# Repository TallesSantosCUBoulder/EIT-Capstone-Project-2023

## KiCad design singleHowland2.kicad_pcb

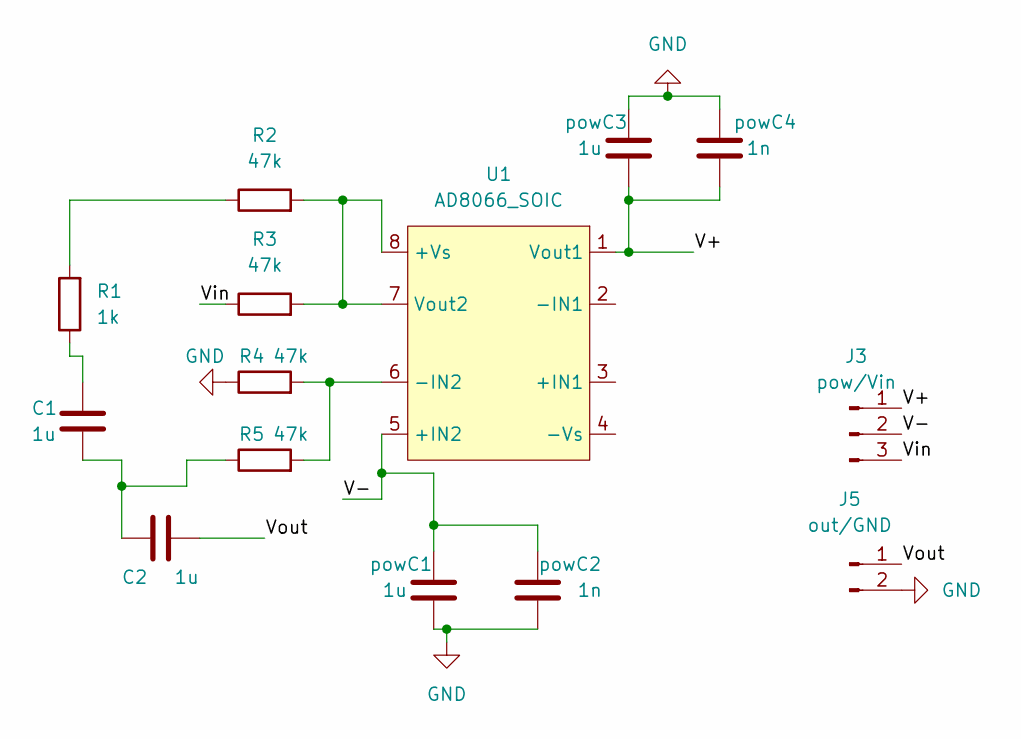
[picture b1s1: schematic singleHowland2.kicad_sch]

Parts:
C1, C2: 1u; R_Axial_DIN0207_L6.3mm_D2.5mm_P7.62mm_Horizontal
J3: pow/Vin; PinHeader_1x03_P2.54mm_Vertical
J5: out/GND; PinHeader_1x02_P2.54mm_Vertical
R1: 1k; R_Axial_DIN0207_L6.3mm_D2.5mm_P7.62mm_Horizontal
R2, R3, R4, R5: 47k; R_Axial_DIN0207_L6.3mm_D2.5mm_P7.62mm_Horizontal
U1: AD8066_SOIC; DIP-8_W7.62mm
powC1, powC3: 1u; R_Axial_DIN0207_L6.3mm_D2.5mm_P7.62mm_Horizontal
powC2, powC4: 1n; R_Axial_DIN0207_L6.3mm_D2.5mm_P7.62mm_Horizontal

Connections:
/V+: J3.1, U1.1 (Vout1), powC3.2, powC4.2
/V-: J3.2, U1.5 (+IN2), powC1.1, powC2.1
/Vin: J3.3, R3.1
/Vout: C2.2, J5.1
GND: J5.2, R4.1, powC1.2, powC2.2, powC3.1, powC4.1
unnamed: C1.1, R1.1
unnamed: C1.2, C2.1, R5.1
unnamed: R1.2, R2.1
unnamed: R2.2, R3.2, U1.7 (Vout2), U1.8 (+Vs)
unnamed: R4.2, R5.2, U1.6 (-IN2)

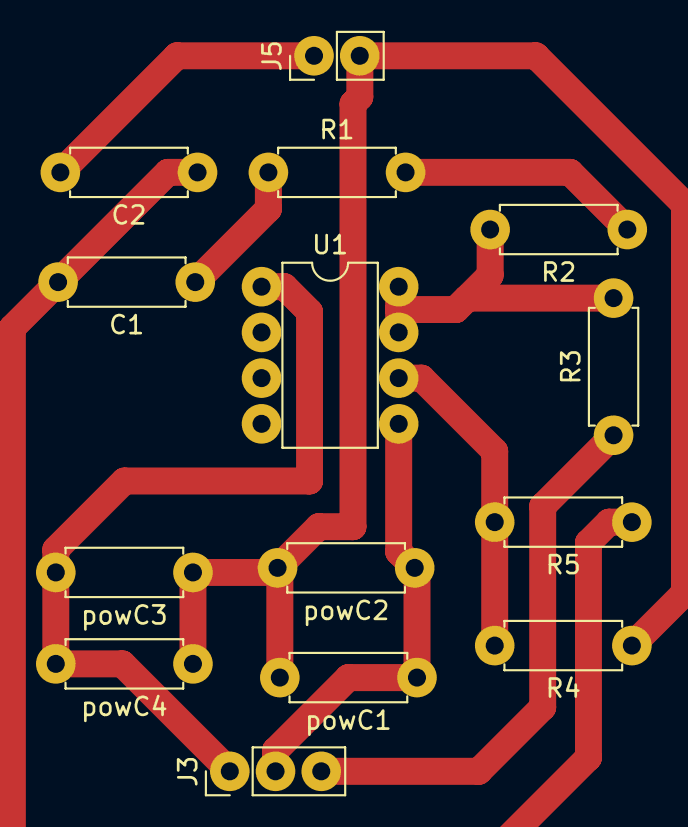
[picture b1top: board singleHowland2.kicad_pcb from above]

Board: 2 copper layers, 14 parts (0 on the bottom side), 10 nets.
